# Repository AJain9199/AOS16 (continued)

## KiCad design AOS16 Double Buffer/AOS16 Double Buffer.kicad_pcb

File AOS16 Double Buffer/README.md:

# Double Buffer
The double buffer is one of the most complicated PCBs in the project. It is a RAM module that serves the important function of facilitating data transfer between the CPU and GPU.

The PCB has two access ports, each consisting of an address and I/O port and 2 control signals to interface with the single RAM chip. The SWP signal determines which port gets to access the memory. 

In the final setup, 2 of these double buffer boards are stacked on top of each other such that they share all inputs and outputs except the SWP signal. The two boards get opposite SWP lines, allowing both ports to access their designated RAM chip. If the SWP line inverts, the physical chip the ports access is exchanged. Both ports can access data written by the other. 

In deployment, one port connects to the AOS CPU while the other connects to the GPU. The CPU writes frame-buffer data and then flips the SWP using a special `swp` instruction, effectively acting as a hardware double-buffer for the video data.

```mermaid
flowchart LR
    ADDR0[\"ADDR0"\]
    IO0[\"IO0"\]
    buf1["Buffer"]
    buf2{{"Transceiver"}}
    sram["SRAM"]
    ADDR1[/"ADDR1"/]
    IO1[/"IO1"/]
    buf3["Buffer"]
    buf4{{"Transceiver"}}
    ctrl["`Control Circuit`"]
    nr0(("nR0"))
    nw0(("nW0"))
    nr1(("nR1"))
    nw1(("nW1"))
    swp(("SWP"))
    ADDR0 --> buf1
    IO0 --> buf2
    buf1 --> sram
    buf2 --> sram
    ADDR1 --> buf3
    IO1 --> buf4
    buf3 --> sram
    buf4 --> sram
    nr0 --> ctrl
    nw0 --> ctrl
    nr1 --> ctrl
    nw1 --> ctrl
    swp --> ctrl
    ctrl -->|"direction, output enable"| buf2
    ctrl -->|"direction, output enable"| buf4
    ctrl -->|"output enable"| buf1
    ctrl -->|"output enable"| buf3
    linkStyle 14 stroke:#aaaaaa,color:#888888
    %% mermaid-flow:pos ADDR0=292,326 IO0=295,462 buf1=482,329 buf2=482,462 sram=693,404 ADDR1=1056,323 IO1=1059,465 buf3=887,323 buf4=884,465 ctrl=689,899 nr0=302,1107 nw0=302,977 nr1=302,847 nw1=302,717 swp=302,587
```

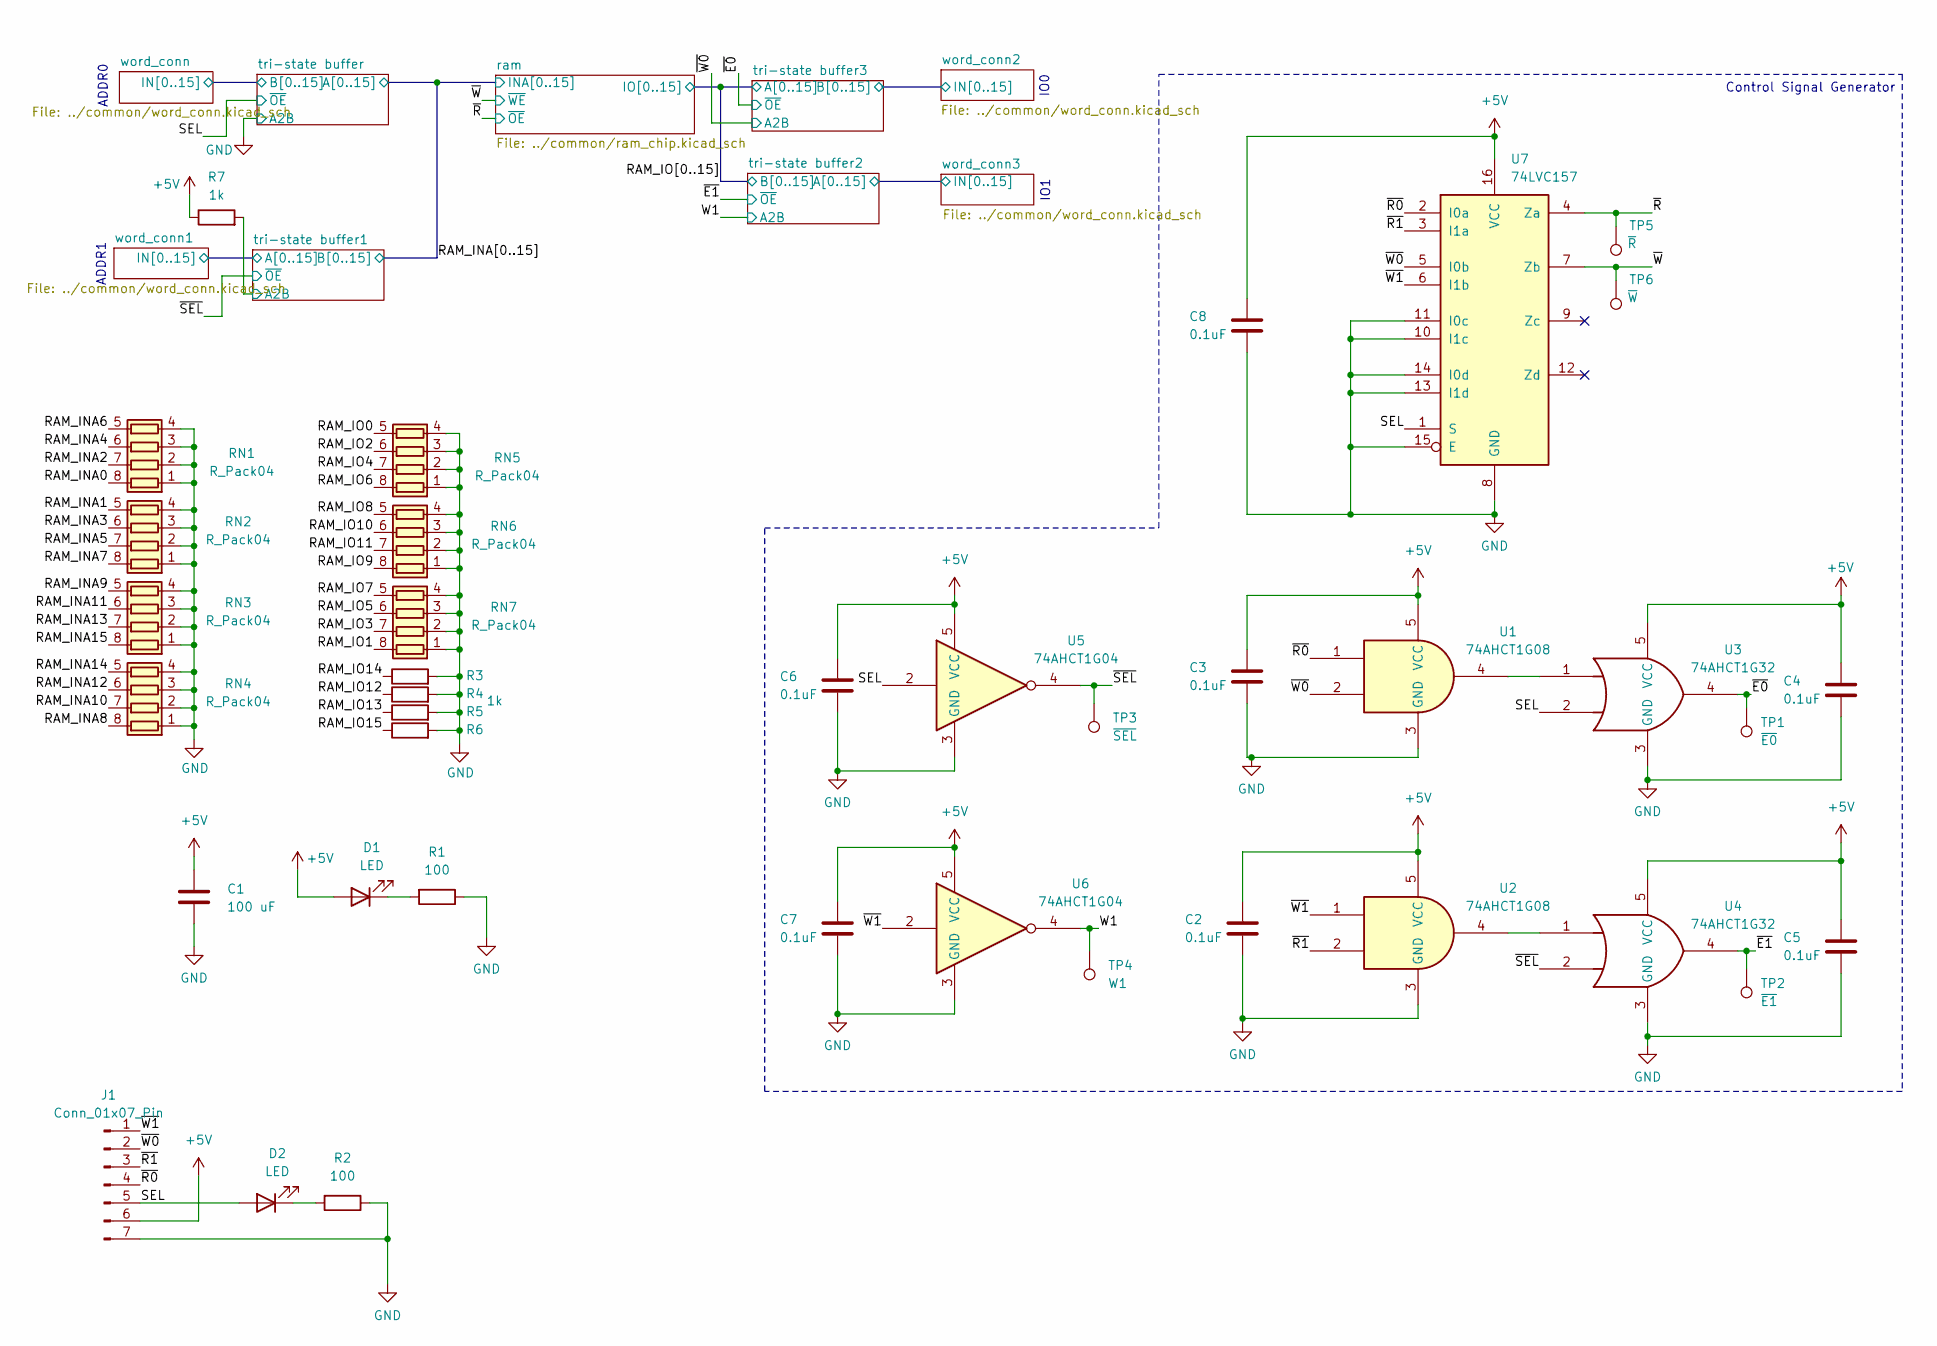
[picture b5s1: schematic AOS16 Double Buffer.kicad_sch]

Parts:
C1: 100 uF; CP_Elec_5x5.3
C2, C3, C4, C5, C6, C7, C8: 0.1uF; C_0603_1608Metric
D1, D2: LED; LED_0603_1608Metric
J1: Conn_01x07_Pin; PinHeader_1x07_P2.54mm_Vertical
R1, R2: 100; R_0603_1608Metric
R3, R4, R5, R6, R7: 1k; R_0603_1608Metric
RN1, RN2, RN3, RN4, RN5, RN6, RN7: R_Pack04; R_Cat16-4
TP1: ~{E0}; TestPoint_Pad_D1.0mm
TP2: ~{E1}; TestPoint_Pad_D1.0mm
TP3: ~{SEL}; TestPoint_Pad_D1.0mm
TP4: W1; TestPoint_Pad_D1.0mm
TP5: ~{R}; TestPoint_Pad_D1.0mm
TP6: ~{W}; TestPoint_Pad_D1.0mm
U1, U2: 74AHCT1G08; SOT-23-5
U3, U4: 74AHCT1G32; SOT-23-5
U5, U6: 74AHCT1G04; SOT-23-5
U7: 74LVC157; SOIC-16_3.9x9.9mm_P1.27mm

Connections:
+5V: C1.1, C2.1, C3.1, C4.1, C5.1, C6.1, C7.1, C8.1, D1.2 (A), J1.6, R7.1, U1.5 (VCC), U2.5 (VCC), U3.5 (VCC), U4.5 (VCC), U5.5 (VCC), U6.5 (VCC), U7.16 (VCC); also elsewhere on the board
/RAM_INA0: RN1.8 (R1.2); also elsewhere on the board
/RAM_INA1: RN2.5 (R4.2); also elsewhere on the board
/RAM_INA2: RN1.7 (R2.2); also elsewhere on the board
/RAM_INA3: RN2.6 (R3.2); also elsewhere on the board
/RAM_INA4: RN1.6 (R3.2); also elsewhere on the board
/RAM_INA5: RN2.7 (R2.2); also elsewhere on the board
/RAM_INA6: RN1.5 (R4.2); also elsewhere on the board
/RAM_INA7: RN2.8 (R1.2); also elsewhere on the board
/RAM_INA8: RN4.8 (R1.2); also elsewhere on the board
/RAM_INA9: RN3.5 (R4.2); also elsewhere on the board
/RAM_INA10: RN4.7 (R2.2); also elsewhere on the board
/RAM_INA11: RN3.6 (R3.2); also elsewhere on the board
/RAM_INA12: RN4.6 (R3.2); also elsewhere on the board
/RAM_INA13: RN3.7 (R2.2); also elsewhere on the board
/RAM_INA14: RN4.5 (R4.2); also elsewhere on the board
/RAM_INA15: RN3.8 (R1.2); also elsewhere on the board
/RAM_IO0: RN5.5 (R4.2); also elsewhere on the board
/RAM_IO1: RN7.8 (R1.2); also elsewhere on the board
/RAM_IO2: RN5.6 (R3.2); also elsewhere on the board
/RAM_IO3: RN7.7 (R2.2); also elsewhere on the board
/RAM_IO4: RN5.7 (R2.2); also elsewhere on the board
/RAM_IO5: RN7.6 (R3.2); also elsewhere on the board
/RAM_IO6: RN5.8 (R1.2); also elsewhere on the board
/RAM_IO7: RN7.5 (R4.2); also elsewhere on the board
/RAM_IO8: RN6.5 (R4.2); also elsewhere on the board
/RAM_IO9: RN6.8 (R1.2); also elsewhere on the board
/RAM_IO10: RN6.6 (R3.2); also elsewhere on the board
/RAM_IO11: RN6.7 (R2.2); also elsewhere on the board
/RAM_IO12: R4.1; also elsewhere on the board
/RAM_IO13: R5.1; also elsewhere on the board
/RAM_IO14: R3.1; also elsewhere on the board
/RAM_IO15: R6.1; also elsewhere on the board
/SEL: D2.2 (A), J1.5, U3.2, U5.2, U7.1 (S); also elsewhere on the board
/W1: TP4.1, U6.4; also elsewhere on the board
/tri-state buffer1/A2B: R7.2; also elsewhere on the board
/~E0: TP1.1, U3.4; also elsewhere on the board
/~E1: TP2.1, U4.4; also elsewhere on the board
/~R0: J1.4, U1.1, U7.2 (I0a)
/~R1: J1.3, U2.2, U7.3 (I1a)
/~R: TP5.1, U7.4 (Za); also elsewhere on the board
/~SEL: TP3.1, U4.2, U5.4; also elsewhere on the board
/~W0: J1.2, U1.2, U7.5 (I0b); also elsewhere on the board
/~W1: J1.1, U2.1, U6.2, U7.6 (I1b)
/~W: TP6.1, U7.7 (Zb); also elsewhere on the board
GND: C1.2, C2.2, C3.2, C4.2, C5.2, C6.2, C7.2, C8.2, J1.7, R1.1, R2.1, R3.2, R4.2, R5.2, R6.2, RN1.1 (R1.1), RN1.2 (R2.1), RN1.3 (R3.1), RN1.4 (R4.1), RN2.1 (R1.1), RN2.2 (R2.1), RN2.3 (R3.1), RN2.4 (R4.1), RN3.1 (R1.1), RN3.2 (R2.1), RN3.3 (R3.1), RN3.4 (R4.1), RN4.1 (R1.1), RN4.2 (R2.1), RN4.3 (R3.1), RN4.4 (R4.1), RN5.1 (R1.1), RN5.2 (R2.1), RN5.3 (R3.1), RN5.4 (R4.1), RN6.1 (R1.1), RN6.2 (R2.1), RN6.3 (R3.1), RN6.4 (R4.1), RN7.1 (R1.1), RN7.2 (R2.1), RN7.3 (R3.1), RN7.4 (R4.1), U1.3 (GND), U2.3 (GND), U3.3 (GND), U4.3 (GND), U5.3 (GND), U6.3 (GND), U7.8 (GND), U7.10 (I1c), U7.11 (I0c), U7.13 (I1d), U7.14 (I0d), U7.15 (E); also elsewhere on the board
unnamed: D1.1 (K), R1.2
unnamed: D2.1 (K), R2.2
unnamed: U1.4, U3.1
unnamed: U2.4, U4.1

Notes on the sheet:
ADDR1
Control Signal Generator
IO1
ADDR0
IO0

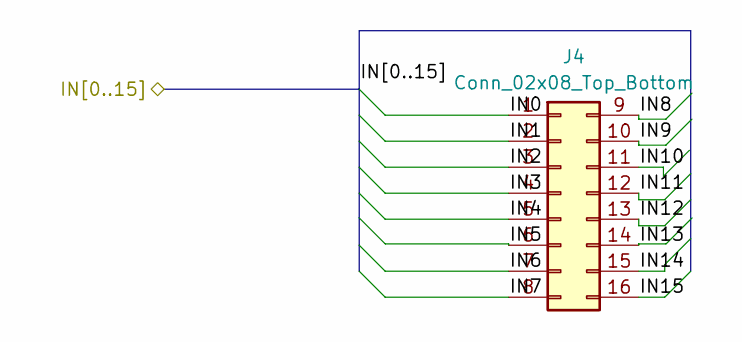
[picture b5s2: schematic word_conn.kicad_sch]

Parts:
J4: Conn_02x08_Top_Bottom; PinHeader_2x08_P2.54mm_Vertical

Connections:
/word_conn2/IN0: J4.1; also elsewhere on the board
/word_conn2/IN1: J4.2; also elsewhere on the board
/word_conn2/IN2: J4.3; also elsewhere on the board
/word_conn2/IN3: J4.4; also elsewhere on the board
/word_conn2/IN4: J4.5; also elsewhere on the board
/word_conn2/IN5: J4.6; also elsewhere on the board
/word_conn2/IN6: J4.7; also elsewhere on the board
/word_conn2/IN7: J4.8; also elsewhere on the board
/word_conn2/IN8: J4.9; also elsewhere on the board
/word_conn2/IN9: J4.10; also elsewhere on the board
/word_conn2/IN10: J4.11; also elsewhere on the board
/word_conn2/IN11: J4.12; also elsewhere on the board
/word_conn2/IN12: J4.13; also elsewhere on the board
/word_conn2/IN13: J4.14; also elsewhere on the board
/word_conn2/IN14: J4.15; also elsewhere on the board
/word_conn2/IN15: J4.16; also elsewhere on the board

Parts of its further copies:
J2, J3, J5: Conn_02x08_Top_Bottom; PinHeader_2x08_P2.54mm_Vertical

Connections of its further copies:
/word_conn1/IN0: J3.1; also elsewhere on the board
/word_conn1/IN1: J3.2; also elsewhere on the board
/word_conn1/IN2: J3.3; also elsewhere on the board
/word_conn1/IN3: J3.4; also elsewhere on the board
/word_conn1/IN4: J3.5; also elsewhere on the board
/word_conn1/IN5: J3.6; also elsewhere on the board
/word_conn1/IN6: J3.7; also elsewhere on the board
/word_conn1/IN7: J3.8; also elsewhere on the board
/word_conn1/IN8: J3.9; also elsewhere on the board
/word_conn1/IN9: J3.10; also elsewhere on the board
/word_conn1/IN10: J3.11; also elsewhere on the board
/word_conn1/IN11: J3.12; also elsewhere on the board
/word_conn1/IN12: J3.13; also elsewhere on the board
/word_conn1/IN13: J3.14; also elsewhere on the board
/word_conn1/IN14: J3.15; also elsewhere on the board
/word_conn1/IN15: J3.16; also elsewhere on the board
/word_conn3/IN0: J5.1; also elsewhere on the board
/word_conn3/IN1: J5.2; also elsewhere on the board
/word_conn3/IN2: J5.3; also elsewhere on the board
/word_conn3/IN3: J5.4; also elsewhere on the board
/word_conn3/IN4: J5.5; also elsewhere on the board
/word_conn3/IN5: J5.6; also elsewhere on the board
/word_conn3/IN6: J5.7; also elsewhere on the board
/word_conn3/IN7: J5.8; also elsewhere on the board
/word_conn3/IN8: J5.9; also elsewhere on the board
/word_conn3/IN9: J5.10; also elsewhere on the board
/word_conn3/IN10: J5.11; also elsewhere on the board
/word_conn3/IN11: J5.12; also elsewhere on the board
/word_conn3/IN12: J5.13; also elsewhere on the board
/word_conn3/IN13: J5.14; also elsewhere on the board
/word_conn3/IN14: J5.15; also elsewhere on the board
/word_conn3/IN15: J5.16; also elsewhere on the board
/word_conn/IN0: J2.1; also elsewhere on the board
/word_conn/IN1: J2.2; also elsewhere on the board
/word_conn/IN2: J2.3; also elsewhere on the board
/word_conn/IN3: J2.4; also elsewhere on the board
/word_conn/IN4: J2.5; also elsewhere on the board
/word_conn/IN5: J2.6; also elsewhere on the board
/word_conn/IN6: J2.7; also elsewhere on the board
/word_conn/IN7: J2.8; also elsewhere on the board
/word_conn/IN8: J2.9; also elsewhere on the board
/word_conn/IN9: J2.10; also elsewhere on the board
/word_conn/IN10: J2.11; also elsewhere on the board
/word_conn/IN11: J2.12; also elsewhere on the board
/word_conn/IN12: J2.13; also elsewhere on the board
/word_conn/IN13: J2.14; also elsewhere on the board
/word_conn/IN14: J2.15; also elsewhere on the board
/word_conn/IN15: J2.16; also elsewhere on the board

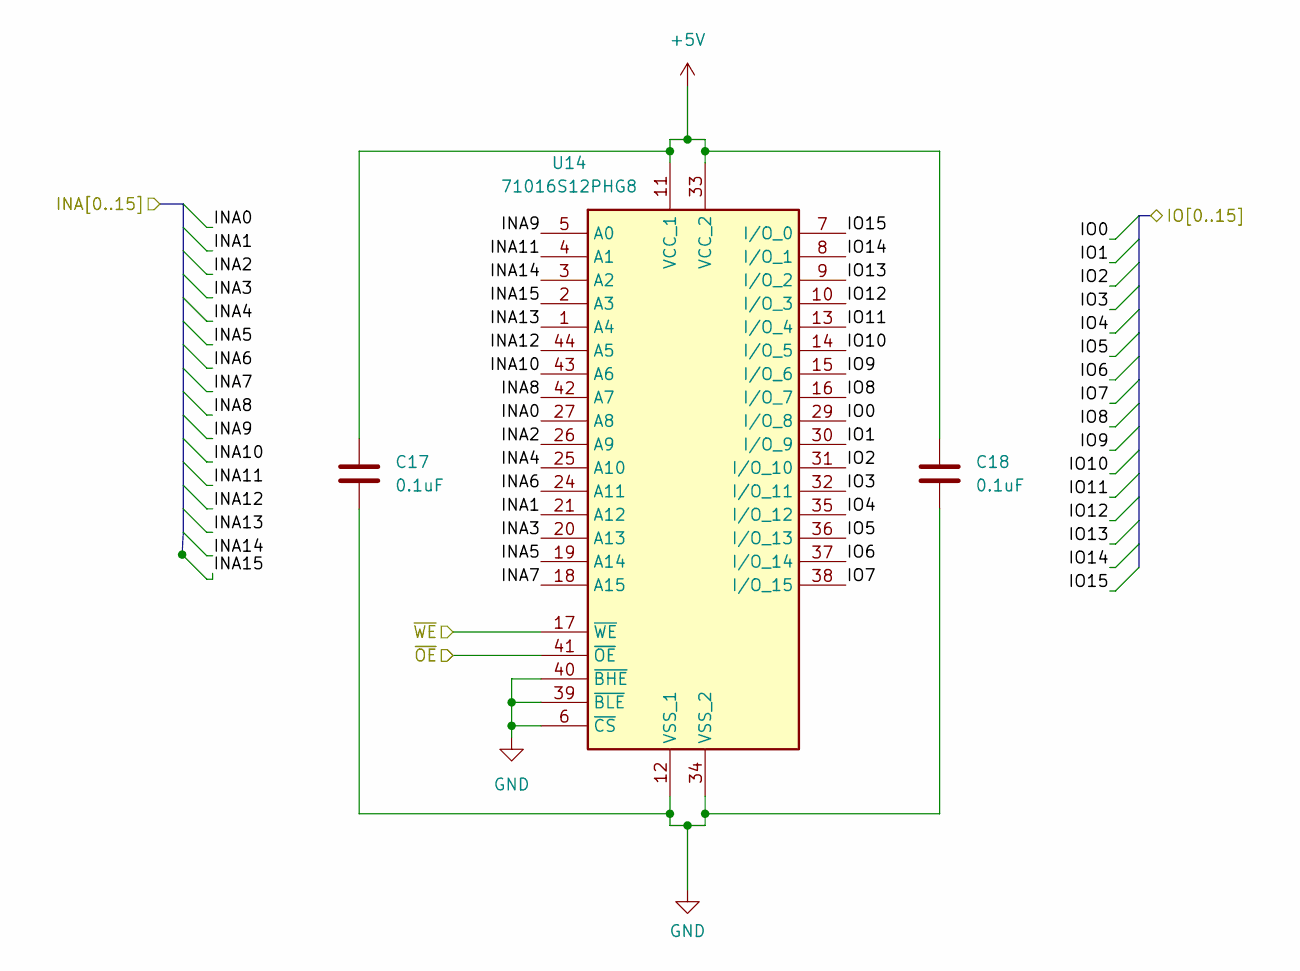
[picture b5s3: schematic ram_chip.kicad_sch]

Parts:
C17, C18: 0.1uF; C_0603_1608Metric
U14: 71016S12PHG8; TSOP-II-44_10.16x18.41mm_P0.8mm; Mouser Part Number 972-71016S12PHG8

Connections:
+5V: C17.1, C18.1; also elsewhere on the board
GND: C17.2, C18.2; also elsewhere on the board

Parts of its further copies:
C9, C10: 0.1uF; C_0603_1608Metric
U8: 71016S12PHG8; TSOP-II-44_10.16x18.41mm_P0.8mm; Mouser Part Number 972-71016S12PHG8

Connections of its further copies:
+5V: C9.1, C10.1, U8.11 (VCC_1), U8.33 (VCC_2); also elsewhere on the board
/RAM_INA0: U8.1 (A4); also elsewhere on the board
/RAM_INA1: U8.44 (A5); also elsewhere on the board
/RAM_INA2: U8.2 (A3); also elsewhere on the board
/RAM_INA3: U8.43 (A6); also elsewhere on the board
/RAM_INA4: U8.3 (A2); also elsewhere on the board
/RAM_INA5: U8.42 (A7); also elsewhere on the board
/RAM_INA6: U8.4 (A1); also elsewhere on the board
/RAM_INA7: U8.5 (A0); also elsewhere on the board
/RAM_INA8: U8.24 (A11); also elsewhere on the board
/RAM_INA9: U8.21 (A12); also elsewhere on the board
/RAM_INA10: U8.25 (A10); also elsewhere on the board
/RAM_INA11: U8.20 (A13); also elsewhere on the board
/RAM_INA12: U8.26 (A9); also elsewhere on the board
/RAM_INA13: U8.19 (A14); also elsewhere on the board
/RAM_INA14: U8.27 (A8); also elsewhere on the board
/RAM_INA15: U8.18 (A15); also elsewhere on the board
/RAM_IO0: U8.7 (I/O_0); also elsewhere on the board
/RAM_IO1: U8.38 (I/O_15); also elsewhere on the board
/RAM_IO2: U8.8 (I/O_1); also elsewhere on the board
/RAM_IO3: U8.37 (I/O_14); also elsewhere on the board
/RAM_IO4: U8.9 (I/O_2); also elsewhere on the board
/RAM_IO5: U8.36 (I/O_13); also elsewhere on the board
/RAM_IO6: U8.10 (I/O_3); also elsewhere on the board
/RAM_IO7: U8.35 (I/O_12); also elsewhere on the board
/RAM_IO8: U8.13 (I/O_4); also elsewhere on the board
/RAM_IO9: U8.32 (I/O_11); also elsewhere on the board
/RAM_IO10: U8.14 (I/O_5); also elsewhere on the board
/RAM_IO11: U8.31 (I/O_10); also elsewhere on the board
/RAM_IO12: U8.15 (I/O_6); also elsewhere on the board
/RAM_IO13: U8.30 (I/O_9); also elsewhere on the board
/RAM_IO14: U8.16 (I/O_7); also elsewhere on the board
/RAM_IO15: U8.29 (I/O_8); also elsewhere on the board
/~R: U8.41 (~OE); also elsewhere on the board
/~W: U8.17 (~WE); also elsewhere on the board
GND: C9.2, C10.2, U8.6 (~CS), U8.12 (VSS_1), U8.34 (VSS_2), U8.39 (~BLE), U8.40 (~BHE); also elsewhere on the board

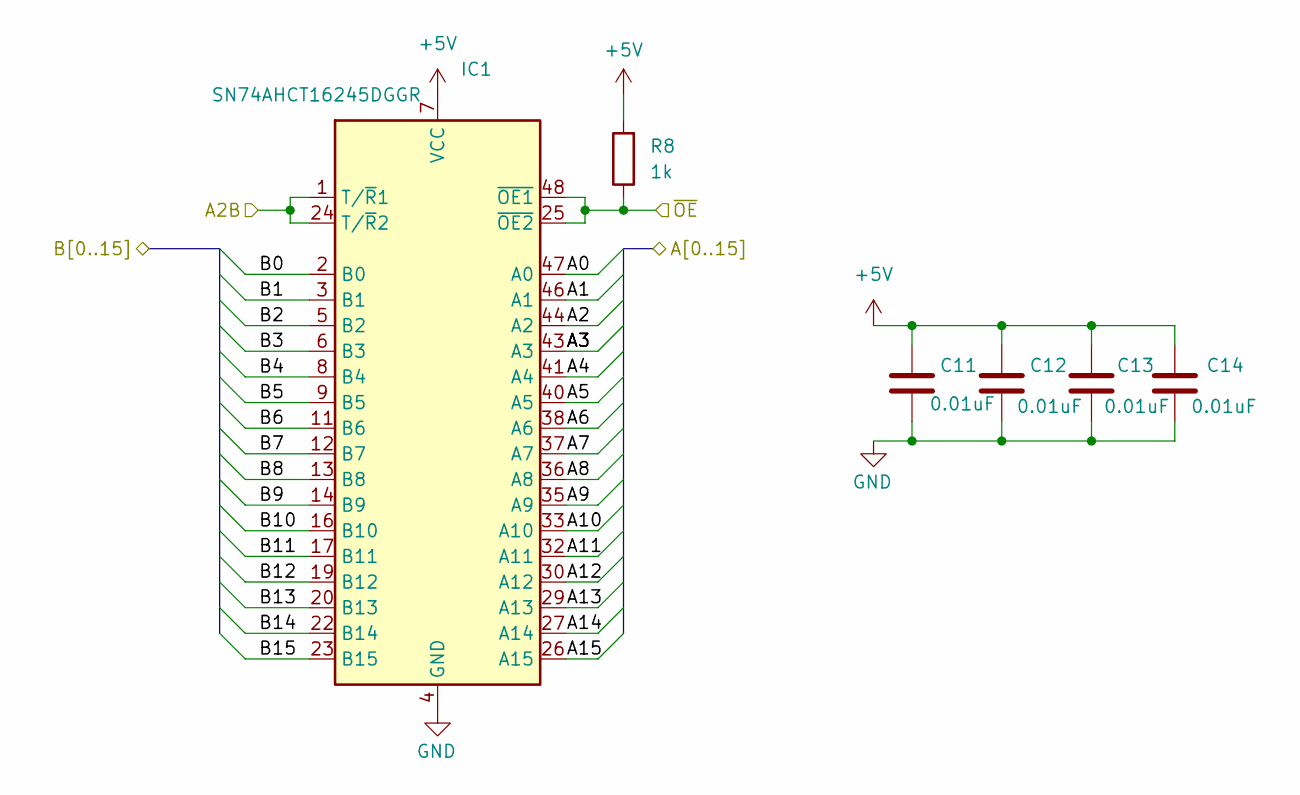
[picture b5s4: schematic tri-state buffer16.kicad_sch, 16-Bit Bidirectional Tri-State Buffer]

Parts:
C11, C12, C13, C14: 0.01uF; C_0603_1608Metric
IC1: SN74AHCT16245DGGR; TSSOP-48_6.1x12.5mm_P0.5mm
R8: 1k; R_0603_1608Metric

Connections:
+5V: C11.1, C12.1, C13.1, C14.1, IC1.7 (VCC), IC1.18 (VCC), IC1.31 (VCC), IC1.42 (VCC), R8.2; also elsewhere on the board
/RAM_INA0: IC1.2 (B0); also elsewhere on the board
/RAM_INA1: IC1.3 (B1); also elsewhere on the board
/RAM_INA2: IC1.5 (B2); also elsewhere on the board
/RAM_INA3: IC1.6 (B3); also elsewhere on the board
/RAM_INA4: IC1.8 (B4); also elsewhere on the board
/RAM_INA5: IC1.9 (B5); also elsewhere on the board
/RAM_INA6: IC1.11 (B6); also elsewhere on the board
/RAM_INA7: IC1.12 (B7); also elsewhere on the board
/RAM_INA8: IC1.13 (B8); also elsewhere on the board
/RAM_INA9: IC1.14 (B9); also elsewhere on the board
/RAM_INA10: IC1.16 (B10); also elsewhere on the board
/RAM_INA11: IC1.17 (B11); also elsewhere on the board
/RAM_INA12: IC1.19 (B12); also elsewhere on the board
/RAM_INA13: IC1.20 (B13); also elsewhere on the board
/RAM_INA14: IC1.22 (B14); also elsewhere on the board
/RAM_INA15: IC1.23 (B15); also elsewhere on the board
/tri-state buffer1/A2B: IC1.1 (T/~R1), IC1.24 (T/~R2); also elsewhere on the board
/word_conn1/IN0: IC1.47 (A0); also elsewhere on the board
/word_conn1/IN1: IC1.46 (A1); also elsewhere on the board
/word_conn1/IN2: IC1.44 (A2); also elsewhere on the board
/word_conn1/IN3: IC1.43 (A3); also elsewhere on the board
/word_conn1/IN4: IC1.41 (A4); also elsewhere on the board
/word_conn1/IN5: IC1.40 (A5); also elsewhere on the board
/word_conn1/IN6: IC1.38 (A6); also elsewhere on the board
/word_conn1/IN7: IC1.37 (A7); also elsewhere on the board
/word_conn1/IN8: IC1.36 (A8); also elsewhere on the board
/word_conn1/IN9: IC1.35 (A9); also elsewhere on the board
/word_conn1/IN10: IC1.33 (A10); also elsewhere on the board
/word_conn1/IN11: IC1.32 (A11); also elsewhere on the board
/word_conn1/IN12: IC1.30 (A12); also elsewhere on the board
/word_conn1/IN13: IC1.29 (A13); also elsewhere on the board
/word_conn1/IN14: IC1.27 (A14); also elsewhere on the board
/word_conn1/IN15: IC1.26 (A15); also elsewhere on the board
/~SEL: IC1.25 (~OE2), IC1.48 (~OE1), R8.1; also elsewhere on the board
GND: C11.2, C12.2, C13.2, C14.2, IC1.4 (GND), IC1.10 (GND), IC1.15 (GND), IC1.21 (GND), IC1.28 (GND), IC1.34 (GND), IC1.39 (GND), IC1.45 (GND); also elsewhere on the board

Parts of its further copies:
C15, C16, C19, C20, C21, C22, C23, C24, C25, C26: 0.01uF; C_0603_1608Metric
IC2, IC3, IC4: SN74AHCT16245DGGR; TSSOP-48_6.1x12.5mm_P0.5mm
R9, R10, R11: 1k; R_0603_1608Metric

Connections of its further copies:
+5V: C15.1, C16.1, C19.1, C20.1, C21.1, C22.1, C23.1, C24.1, C25.1, C26.1, IC2.7 (VCC), IC2.18 (VCC), IC2.31 (VCC), IC2.42 (VCC), IC3.7 (VCC), IC3.18 (VCC), IC3.31 (VCC), IC3.42 (VCC), IC4.7 (VCC), IC4.18 (VCC), IC4.31 (VCC), IC4.42 (VCC), R9.2, R10.2, R11.2; also elsewhere on the board
/RAM_INA0: IC4.47 (A0); also elsewhere on the board
/RAM_INA1: IC4.46 (A1); also elsewhere on the board
/RAM_INA2: IC4.44 (A2); also elsewhere on the board
/RAM_INA3: IC4.43 (A3); also elsewhere on the board
/RAM_INA4: IC4.41 (A4); also elsewhere on the board
/RAM_INA5: IC4.40 (A5); also elsewhere on the board
/RAM_INA6: IC4.38 (A6); also elsewhere on the board
/RAM_INA7: IC4.37 (A7); also elsewhere on the board
/RAM_INA8: IC4.36 (A8); also elsewhere on the board
/RAM_INA9: IC4.35 (A9); also elsewhere on the board
/RAM_INA10: IC4.33 (A10); also elsewhere on the board
/RAM_INA11: IC4.32 (A11); also elsewhere on the board
/RAM_INA12: IC4.30 (A12); also elsewhere on the board
/RAM_INA13: IC4.29 (A13); also elsewhere on the board
/RAM_INA14: IC4.27 (A14); also elsewhere on the board
/RAM_INA15: IC4.26 (A15); also elsewhere on the board
/RAM_IO0: IC2.2 (B0), IC3.47 (A0); also elsewhere on the board
/RAM_IO1: IC2.3 (B1), IC3.46 (A1); also elsewhere on the board
/RAM_IO2: IC2.5 (B2), IC3.44 (A2); also elsewhere on the board
/RAM_IO3: IC2.6 (B3), IC3.43 (A3); also elsewhere on the board
/RAM_IO4: IC2.8 (B4), IC3.41 (A4); also elsewhere on the board
/RAM_IO5: IC2.9 (B5), IC3.40 (A5); also elsewhere on the board
/RAM_IO6: IC2.11 (B6), IC3.38 (A6); also elsewhere on the board
/RAM_IO7: IC2.12 (B7), IC3.37 (A7); also elsewhere on the board
/RAM_IO8: IC2.13 (B8), IC3.36 (A8); also elsewhere on the board
/RAM_IO9: IC2.14 (B9), IC3.35 (A9); also elsewhere on the board
/RAM_IO10: IC2.16 (B10), IC3.33 (A10); also elsewhere on the board
/RAM_IO11: IC2.17 (B11), IC3.32 (A11); also elsewhere on the board
/RAM_IO12: IC2.19 (B12), IC3.30 (A12); also elsewhere on the board
/RAM_IO13: IC2.20 (B13), IC3.29 (A13); also elsewhere on the board
/RAM_IO14: IC2.22 (B14), IC3.27 (A14); also elsewhere on the board
/RAM_IO15: IC2.23 (B15), IC3.26 (A15); also elsewhere on the board
/SEL: IC4.25 (~OE2), IC4.48 (~OE1), R11.1; also elsewhere on the board
/W1: IC2.1 (T/~R1), IC2.24 (T/~R2); also elsewhere on the board
/word_conn2/IN0: IC3.2 (B0); also elsewhere on the board
/word_conn2/IN1: IC3.3 (B1); also elsewhere on the board
/word_conn2/IN2: IC3.5 (B2); also elsewhere on the board
/word_conn2/IN3: IC3.6 (B3); also elsewhere on the board
/word_conn2/IN4: IC3.8 (B4); also elsewhere on the board
/word_conn2/IN5: IC3.9 (B5); also elsewhere on the board
/word_conn2/IN6: IC3.11 (B6); also elsewhere on the board
/word_conn2/IN7: IC3.12 (B7); also elsewhere on the board
/word_conn2/IN8: IC3.13 (B8); also elsewhere on the board
/word_conn2/IN9: IC3.14 (B9); also elsewhere on the board
/word_conn2/IN10: IC3.16 (B10); also elsewhere on the board
/word_conn2/IN11: IC3.17 (B11); also elsewhere on the board
/word_conn2/IN12: IC3.19 (B12); also elsewhere on the board
/word_conn2/IN13: IC3.20 (B13); also elsewhere on the board
/word_conn2/IN14: IC3.22 (B14); also elsewhere on the board
/word_conn2/IN15: IC3.23 (B15); also elsewhere on the board
/word_conn3/IN0: IC2.47 (A0); also elsewhere on the board
/word_conn3/IN1: IC2.46 (A1); also elsewhere on the board
/word_conn3/IN2: IC2.44 (A2); also elsewhere on the board
/word_conn3/IN3: IC2.43 (A3); also elsewhere on the board
/word_conn3/IN4: IC2.41 (A4); also elsewhere on the board
/word_conn3/IN5: IC2.40 (A5); also elsewhere on the board
/word_conn3/IN6: IC2.38 (A6); also elsewhere on the board
/word_conn3/IN7: IC2.37 (A7); also elsewhere on the board
/word_conn3/IN8: IC2.36 (A8); also elsewhere on the board
/word_conn3/IN9: IC2.35 (A9); also elsewhere on the board
/word_conn3/IN10: IC2.33 (A10); also elsewhere on the board
/word_conn3/IN11: IC2.32 (A11); also elsewhere on the board
/word_conn3/IN12: IC2.30 (A12); also elsewhere on the board
/word_conn3/IN13: IC2.29 (A13); also elsewhere on the board
/word_conn3/IN14: IC2.27 (A14); also elsewhere on the board
/word_conn3/IN15: IC2.26 (A15); also elsewhere on the board
/word_conn/IN0: IC4.2 (B0); also elsewhere on the board
/word_conn/IN1: IC4.3 (B1); also elsewhere on the board
/word_conn/IN2: IC4.5 (B2); also elsewhere on the board
/word_conn/IN3: IC4.6 (B3); also elsewhere on the board
/word_conn/IN4: IC4.8 (B4); also elsewhere on the board
/word_conn/IN5: IC4.9 (B5); also elsewhere on the board
/word_conn/IN6: IC4.11 (B6); also elsewhere on the board
/word_conn/IN7: IC4.12 (B7); also elsewhere on the board
/word_conn/IN8: IC4.13 (B8); also elsewhere on the board
/word_conn/IN9: IC4.14 (B9); also elsewhere on the board
/word_conn/IN10: IC4.16 (B10); also elsewhere on the board
/word_conn/IN11: IC4.17 (B11); also elsewhere on the board
/word_conn/IN12: IC4.19 (B12); also elsewhere on the board
/word_conn/IN13: IC4.20 (B13); also elsewhere on the board
/word_conn/IN14: IC4.22 (B14); also elsewhere on the board
/word_conn/IN15: IC4.23 (B15); also elsewhere on the board
/~E0: IC3.25 (~OE2), IC3.48 (~OE1), R10.1; also elsewhere on the board
/~E1: IC2.25 (~OE2), IC2.48 (~OE1), R9.1; also elsewhere on the board
/~W0: IC3.1 (T/~R1), IC3.24 (T/~R2); also elsewhere on the board
GND: C15.2, C16.2, C19.2, C20.2, C21.2, C22.2, C23.2, C24.2, C25.2, C26.2, IC2.4 (GND), IC2.10 (GND), IC2.15 (GND), IC2.21 (GND), IC2.28 (GND), IC2.34 (GND), IC2.39 (GND), IC2.45 (GND), IC3.4 (GND), IC3.10 (GND), IC3.15 (GND), IC3.21 (GND), IC3.28 (GND), IC3.34 (GND), IC3.39 (GND), IC3.45 (GND), IC4.1 (T/~R1), IC4.4 (GND), IC4.10 (GND), IC4.15 (GND), IC4.21 (GND), IC4.24 (T/~R2), IC4.28 (GND), IC4.34 (GND), IC4.39 (GND), IC4.45 (GND); also elsewhere on the board

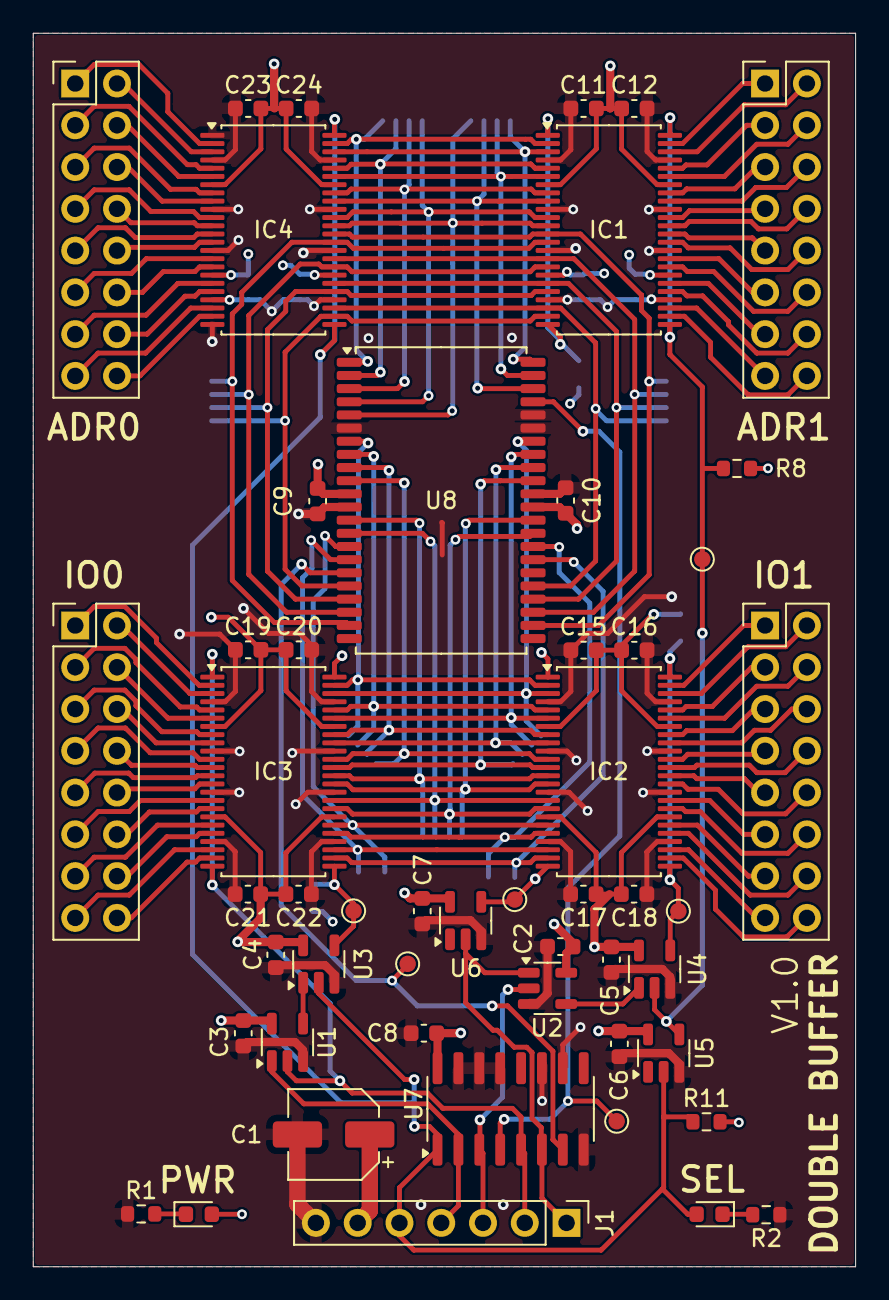
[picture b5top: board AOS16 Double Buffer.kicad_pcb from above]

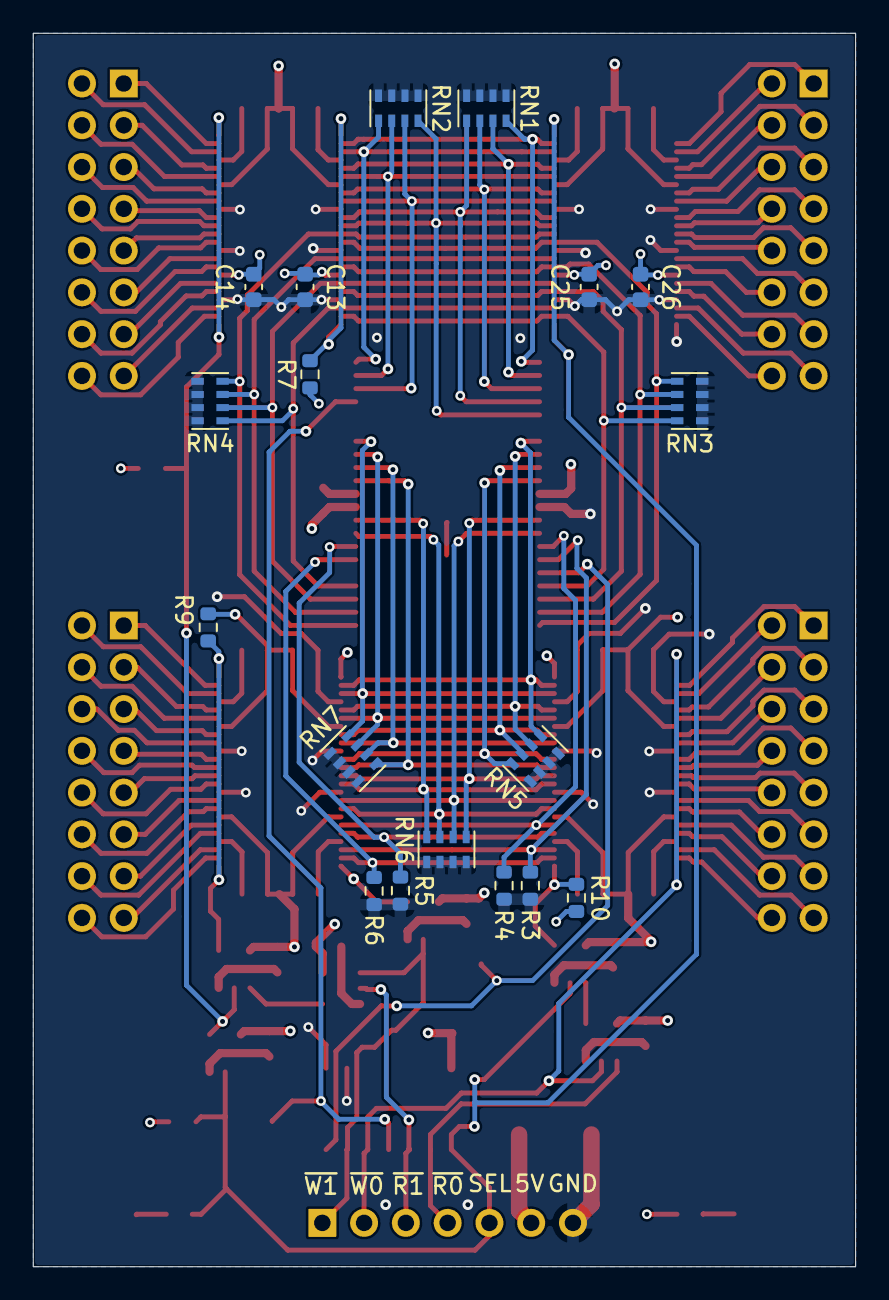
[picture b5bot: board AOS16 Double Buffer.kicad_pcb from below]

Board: 4 copper layers, 50.0 x 75.0 mm, 69 parts (18 on the bottom side), 114 nets.
